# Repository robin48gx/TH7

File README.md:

# TH7
Code to read up to seven thermocouple inputs  from the raspberry pi using the SDS TH7 PCB

Enable spi in raspi-config.

Also, if you are running the pi as a user other than 'pi' add yourself to the spi group 
in /etc/group.

Clone the git hub repo here,

    $ git clone https://github.com/robin48gx/TH7.git 

change directory to TH7 and then run

    $ python ssh_terminal_TH7.py

The python file ssh_terminal_TH7.py is a simple terminal program
that displays the microvolts received from
the thermocouples and displays them in centigrade (for `k` type).
It also displays the PCB temperature and  the Vcc (voltage from USB to the pi;
the value is necessary for accurate calculation of microvolts).
It also creates a logging file (called 'TH7.log') showing the voltage supplied to the pi, the 
PCB temperature and the temperature of each connected thermocouple. This logs once per minute.
If logging is required run with nohup, i.e.

    $ nohup python TH7_logger.py > /dev/null & 
    
The logging will then continue on the pi even if the terminal running it is closed.
The LEDs are controlled by the ssh_terminal_TH7.py and by the TH7_logger.py programs, so if they are alternately blinking
this means the logging is continuing.
A script called 'plot_it.sh' will (using gnuplot) take data from the TH7.log file
and present it as a graph.

The python file thermometers_TH7.py adds to this with 
tkinter drawn thermometers. You may need the tkinter python 
modules for this : i.e. apt-get install python-tk.

Feel free to branch off this to make a temperature logger or a web interface.

For h/w 0.4 and above, an open thermocouple connection will display a very low 
micro-volts figure (typically < -7000) which is out of range for most thermocouples
and out of the range that most temperature readings would ever require (its below
abs zero for a k type for instance).
This means open thermocouples can be error flagged (as has been implemented for the
python `k` type thermocouple in this repo).

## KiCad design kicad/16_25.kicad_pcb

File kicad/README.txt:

The TH7 project in these files is named test.
It is at hardware revision 0.3

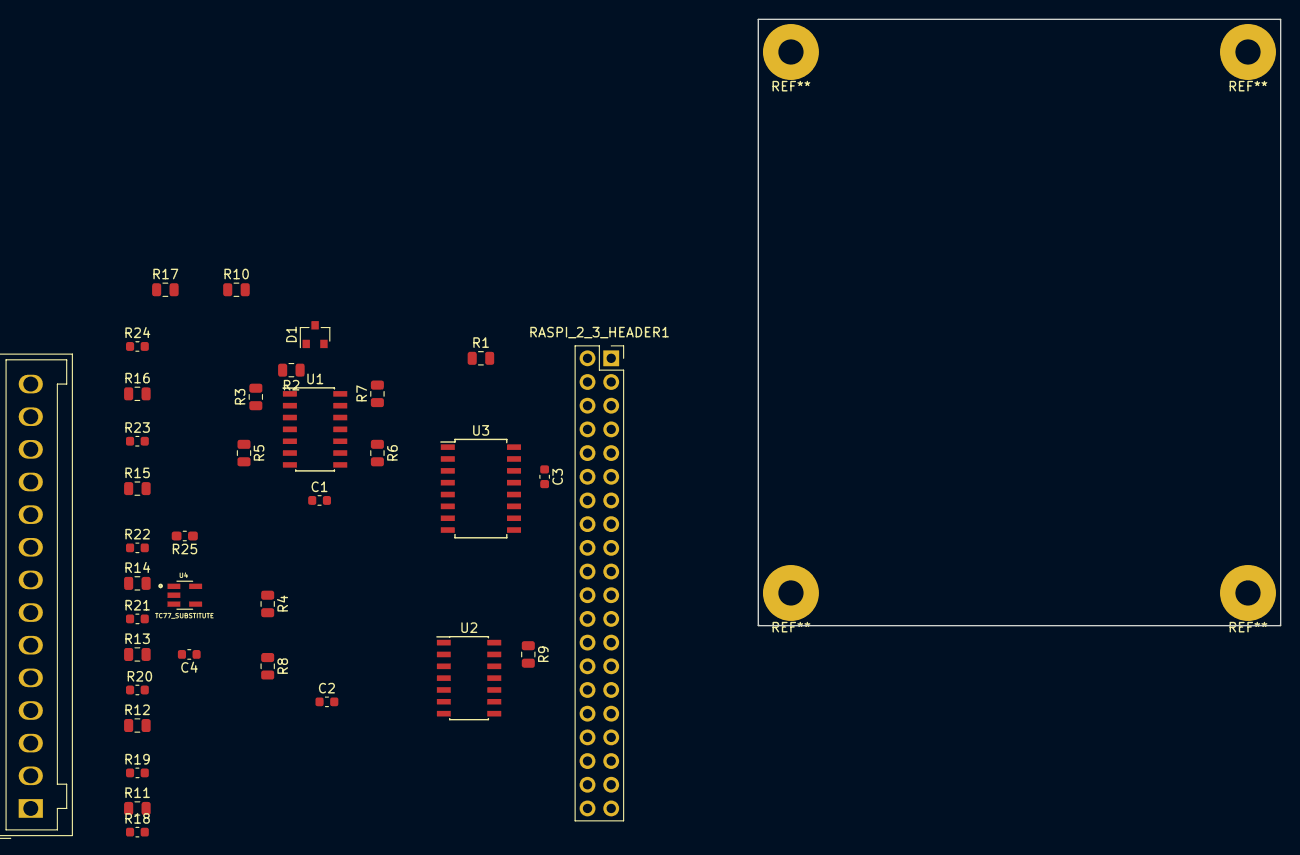
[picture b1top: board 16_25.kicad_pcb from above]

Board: 2 copper layers, 56.0 x 65.0 mm, 36 parts (0 on the bottom side), 44 nets, no tracks yet.

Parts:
C1, C2, C3, C4: 100nF; C_0603_1608Metric
D1: LM4040DBZ-4.1; SOT-23
J1: Screw_Terminal_01x14; Wago_734-144_1x14_P3.50mm_Vertical
R1: 470; R_0805_2012Metric
R2, R3: 10k; R_0805_2012Metric
R4: 200K; R_0805_2012Metric
R5, R6, R7: 100K; R_0805_2012Metric
R8, R10: 200k; R_0805_2012Metric
R9: 500k; R_0805_2012Metric
R11: 1K; R_0805_2012Metric
R12, R13, R14, R15, R16, R17: 1k; R_0805_2012Metric
R18, R19, R20, R21, R22, R23, R24: 500K; R_0603_1608Metric
R25: 10K; R_0603_1608Metric_Pad1.05x0.95mm_HandSolder
RASPI_2_3_HEADER1: Raspberry_Pi_2_3; PinSocket_2x20_P2.54mm_Vertical
U1, U2: MCP6074-E_SL; SOIC-14_3.9x8.7mm_P1.27mm
U3: MCP3208; SOIC-16W_5.3x10.2mm_P1.27mm
U4: TC77_SUBSTITUTE; SOT95P280X145-5N

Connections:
4V096: R3.2, R18.2, R19.2, R20.2, R21.2, R22.2, R23.2, R24.2, U1.1, U1.5, U1.10, U1.12, U2.3, U2.5, U2.10, U2.12, U3.1
unnamed: C1.1, C2.1, RASPI_2_3_HEADER1.4, RASPI_2_3_HEADER1.39, U1.4, U2.4
unnamed: C1.2, C2.2, RASPI_2_3_HEADER1.25, U1.11, U2.11
unnamed: C3.1, C4.1, R1.2, RASPI_2_3_HEADER1.2, U3.15, U3.16, U4.5
unnamed: C3.2, RASPI_2_3_HEADER1.30, U3.9
unnamed: C4.2, R25.2, RASPI_2_3_HEADER1.20, U4.2
unnamed: D1.1, R1.1, R2.2
unnamed: D1.2, RASPI_2_3_HEADER1.6
unnamed: J1.1, R18.1
unnamed: J1.2, R11.1
unnamed: J1.3, R19.1
unnamed: J1.4, R12.1
unnamed: J1.5, R20.1
unnamed: J1.6, R13.1
unnamed: J1.7, R21.1
unnamed: J1.8, R14.1
unnamed: J1.9, R22.1
unnamed: J1.10, R15.1
unnamed: J1.11, R23.1
unnamed: J1.12, R16.1
unnamed: J1.13, R24.1
unnamed: J1.14, R17.1
unnamed: R2.1, U1.3
unnamed: R3.1, U1.2
unnamed: R4.1, U2.1, U3.5
unnamed: R5.2, U1.7, U3.2
unnamed: R6.2, U1.8, U3.3
unnamed: R7.2, U1.14, U3.4
unnamed: R8.2, U2.7
unnamed: R9.1, U2.14
unnamed: R10.1, R17.2, U2.9, U3.7
unnamed: R10.2, U2.8
unnamed: R9.2, R11.2, U2.13, U3.8
unnamed: R5.1, R12.2, U1.6
unnamed: R6.1, R13.2, U1.9
unnamed: R7.1, R14.2, U1.13
unnamed: R4.2, R15.2, U2.2
unnamed: R8.1, R16.2, U2.6, U3.6
unnamed: R25.1, RASPI_2_3_HEADER1.21, U3.12, U4.4
unnamed: RASPI_2_3_HEADER1.19, U3.11
unnamed: RASPI_2_3_HEADER1.23, U3.13, U4.3
unnamed: RASPI_2_3_HEADER1.24, U3.10
unnamed: RASPI_2_3_HEADER1.26, U4.1
unnamed: RASPI_2_3_HEADER1.34, U3.14

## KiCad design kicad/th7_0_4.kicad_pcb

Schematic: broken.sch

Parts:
C1, C2, C3, C4: 100nF; C_0603_1608Metric
D1: LM4040DBZ-4.1; SOT-23
D2, D3: LED_ALT; LED_0805_2012Metric_Pad1.15x1.40mm_HandSolder
J1: Screw_Terminal_01x14; Wago_734-144_1x14_P3.50mm_Vertical
R1: 470; R_0805_2012Metric
R2, R3: 10k; R_0805_2012Metric
R4, R5, R6, R7, R8, R9, R10: 100K; R_0805_2012Metric
R11: 1K; R_0805_2012Metric
R12, R13, R14, R15, R16, R17: 1k; R_0805_2012Metric
R18, R19: 330; R_0805_2012Metric
R25: 10K; R_0603_1608Metric_Pad1.05x0.95mm_HandSolder
R31, R32, R33, R34, R35, R36, R37: 330k; R_0805_2012Metric
RASPI_2_3_HEADER1: Raspberry_Pi_2_3; PinSocket_2x20_P2.54mm_Vertical
U1, U2: MCP6074-E_SL; SOIC-14_3.9x8.7mm_P1.27mm
U3: MCP3208; SOIC-16W_5.3x10.2mm_P1.27mm
U4: TC77_SUBSTITUTE; SOT95P280X145-5N

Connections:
4V096: U1.1 (VOUTA), U1.5 (VINB+), U1.10 (VINC+), U1.12 (VIND+), U2.3 (VINA+), U2.5 (VINB+), U2.10 (VINC+), U2.12 (VIND+); also elsewhere on the board
5V: U1.4 (VDD), U2.4 (VDD), U4.5 (Vdd); also elsewhere on the board
CE1: U4.1 (CS); also elsewhere on the board
MISO_0: U4.4 (SIO); also elsewhere on the board
unnamed 18: U1.3 (VINA+); also elsewhere on the board
unnamed 19: U1.2 (VINA); also elsewhere on the board
unnamed 20: U2.1 (VOUTA); also elsewhere on the board
unnamed 21: U1.7 (VOUTB); also elsewhere on the board
unnamed 22: U1.8 (VOUTC); also elsewhere on the board
unnamed 23: U1.14 (VOUTD); also elsewhere on the board
unnamed 24: U2.7 (VOUTB); also elsewhere on the board
unnamed 25: U2.14 (VOUTD); also elsewhere on the board
unnamed 26: U2.9 (VINC); also elsewhere on the board
unnamed 27: U2.8 (VOUTC); also elsewhere on the board
unnamed 28: U2.13 (VIND); also elsewhere on the board
unnamed 29: U1.6 (VINB); also elsewhere on the board
unnamed 30: U1.9 (VINC); also elsewhere on the board
unnamed 31: U1.13 (VIND); also elsewhere on the board
unnamed 32: U2.2 (VINA); also elsewhere on the board
unnamed 33: U2.6 (VINB); also elsewhere on the board
SCLK0: U4.3 (SCK); also elsewhere on the board

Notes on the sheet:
Revision 0.4 330k disconnection resistors

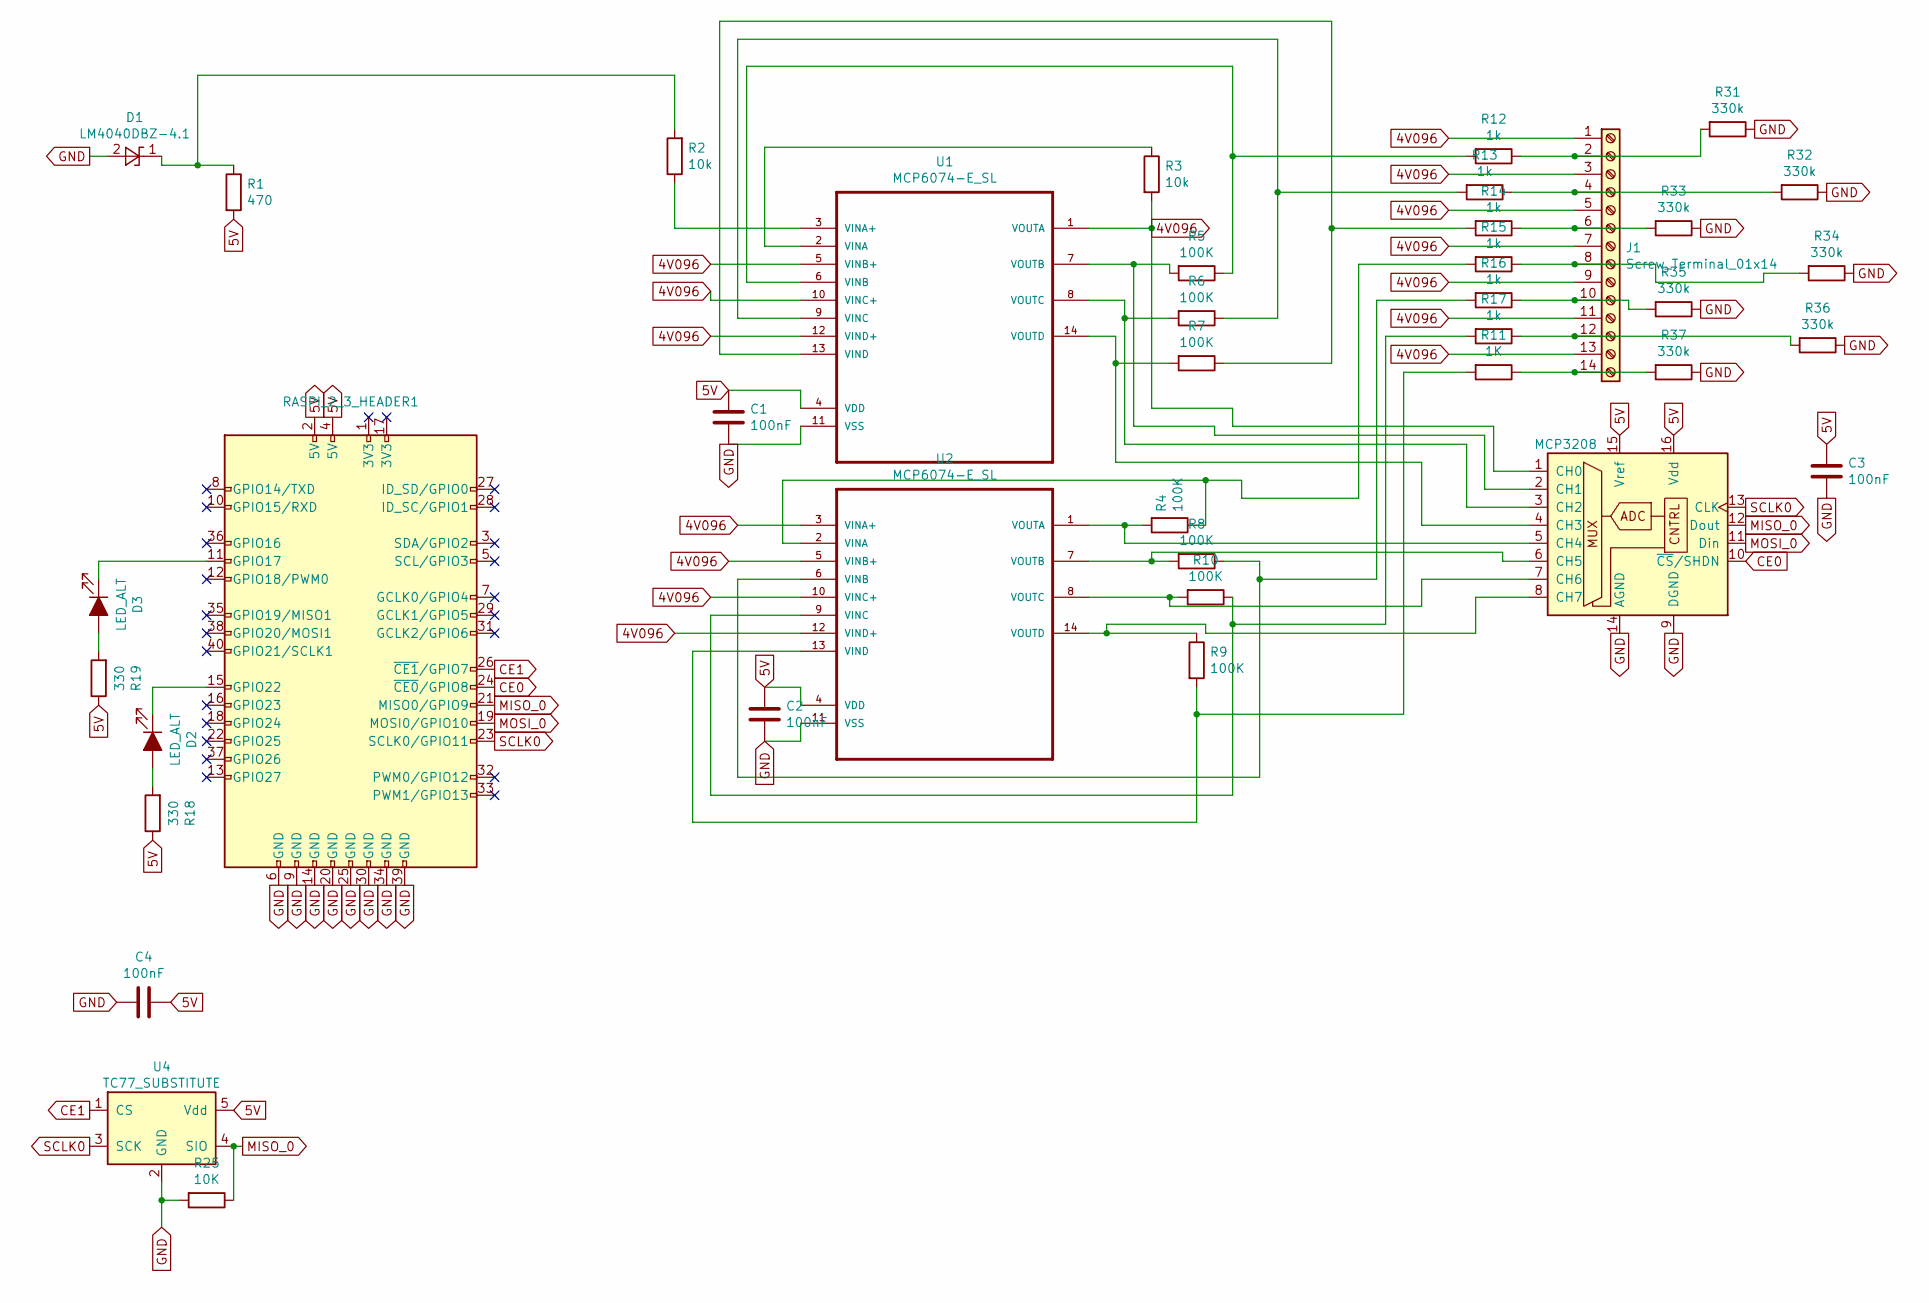
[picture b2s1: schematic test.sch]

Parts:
C1, C2, C3, C4: 100nF; C_0603_1608Metric
D1: LM4040DBZ-4.1; SOT-23
D2, D3: LED_ALT; LED_0805_2012Metric_Pad1.15x1.40mm_HandSolder
J1: Screw_Terminal_01x14; Wago_734-144_1x14_P3.50mm_Vertical
R1: 470; R_0805_2012Metric
R2, R3: 10k; R_0805_2012Metric
R4, R5, R6, R7, R8, R9, R10: 100K; R_0805_2012Metric
R11: 1K; R_0805_2012Metric
R12, R13, R14, R15, R16, R17: 1k; R_0805_2012Metric
R18, R19: 330; R_0805_2012Metric
R25: 10K; R_0603_1608Metric_Pad1.05x0.95mm_HandSolder
R31, R32, R33, R34, R35, R36, R37: 330k; R_0805_2012Metric
RASPI_2_3_HEADER1: Raspberry_Pi_2_3; PinSocket_2x20_P2.54mm_Vertical
U1, U2: MCP6074-E_SL; SOIC-14_3.9x8.7mm_P1.27mm
U3: MCP3208; SOIC-16W_5.3x10.2mm_P1.27mm
U4: TC77_SUBSTITUTE; SOT95P280X145-5N

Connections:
4V096: J1.1, J1.3, J1.5, J1.7, J1.9, J1.11, J1.13, R3.2, U1.1 (VOUTA), U1.5 (VINB+), U1.10 (VINC+), U1.12 (VIND+), U2.3 (VINA+), U2.5 (VINB+), U2.10 (VINC+), U2.12 (VIND+), U3.1 (CH0); also elsewhere on the board
5V: C1.1, C2.1, C3.1, C4.1, R1.2, R18.1, R19.1, RASPI_2_3_HEADER1.2 (5V), RASPI_2_3_HEADER1.4 (5V), U1.4 (VDD), U2.4 (VDD), U3.15 (Vref), U3.16 (Vdd), U4.5 (Vdd); also elsewhere on the board
CE0: RASPI_2_3_HEADER1.24 (~CE0~/GPIO8), U3.10 (~CS~/SHDN)
CE1: RASPI_2_3_HEADER1.26 (~CE1~/GPIO7), U4.1 (CS)
MISO_0: R25.1, RASPI_2_3_HEADER1.21 (MISO0/GPIO9), U3.12 (Dout), U4.4 (SIO)
MOSI_0: RASPI_2_3_HEADER1.19 (MOSI0/GPIO10), U3.11 (Din)
unnamed: D1.1 (K), R1.1, R2.2
unnamed: D2.1 (K), RASPI_2_3_HEADER1.15 (GPIO22)
unnamed: D2.2 (A), R18.2
unnamed: D3.1 (K), RASPI_2_3_HEADER1.11 (GPIO17)
unnamed: D3.2 (A), R19.2
unnamed: J1.2, R12.1, R31.2
unnamed: J1.4, R13.1, R32.2
unnamed: J1.6, R14.1, R33.2
unnamed: J1.8, R15.1, R34.2
unnamed: J1.10, R16.1, R35.2
unnamed: J1.12, R17.1, R36.2
unnamed: J1.14, R11.1, R37.2
unnamed: R2.1, U1.3 (VINA+)
unnamed: R3.1, U1.2 (VINA)
unnamed: R4.2, U2.1 (VOUTA), U3.5 (CH4)
unnamed: R5.2, U1.7 (VOUTB), U3.2 (CH1)
unnamed: R6.2, U1.8 (VOUTC), U3.3 (CH2)
unnamed: R7.2, U1.14 (VOUTD), U3.4 (CH3)
unnamed: R8.2, U2.7 (VOUTB), U3.6 (CH5)
unnamed: R9.1, U2.14 (VOUTD), U3.8 (CH7)
unnamed: R10.1, R17.2, U2.9 (VINC)
unnamed: R10.2, U2.8 (VOUTC), U3.7 (CH6)
unnamed: R9.2, R11.2, U2.13 (VIND)
unnamed: R5.1, R12.2, U1.6 (VINB)
unnamed: R6.1, R13.2, U1.9 (VINC)
unnamed: R7.1, R14.2, U1.13 (VIND)
unnamed: R4.1, R15.2, U2.2 (VINA)
unnamed: R8.1, R16.2, U2.6 (VINB)
SCLK0: RASPI_2_3_HEADER1.23 (SCLK0/GPIO11), U3.13 (CLK), U4.3 (SCK)

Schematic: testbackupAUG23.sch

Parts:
C1, C2, C3, C4: 100nF; C_0603_1608Metric
D1: LM4040DBZ-4.1; SOT-23
J1: Screw_Terminal_01x14; Wago_734-144_1x14_P3.50mm_Vertical
R1: 470; R_0805_2012Metric
R2, R3: 10k; R_0805_2012Metric
R4, R5, R6, R7, R8, R9, R10: 100K; R_0805_2012Metric
R11: 1K; R_0805_2012Metric
R12, R13, R14, R15, R16, R17: 1k; R_0805_2012Metric
R25: 10K; R_0603_1608Metric_Pad1.05x0.95mm_HandSolder
RASPI_2_3_HEADER1: Raspberry_Pi_2_3; PinSocket_2x20_P2.54mm_Vertical
U1, U2: MCP6074-E_SL; SOIC-14_3.9x8.7mm_P1.27mm
U3: MCP3208; SOIC-16W_5.3x10.2mm_P1.27mm
U4: TC77_SUBSTITUTE; SOT95P280X145-5N

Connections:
4V096: U1.1 (VOUTA), U1.5 (VINB+), U1.10 (VINC+), U1.12 (VIND+), U2.3 (VINA+), U2.5 (VINB+), U2.10 (VINC+), U2.12 (VIND+); also elsewhere on the board
5V: U1.4 (VDD), U2.4 (VDD); also elsewhere on the board
unnamed 18: U1.3 (VINA+); also elsewhere on the board
unnamed 19: U1.2 (VINA); also elsewhere on the board
unnamed 20: U2.1 (VOUTA); also elsewhere on the board
unnamed 21: U1.7 (VOUTB); also elsewhere on the board
unnamed 22: U1.8 (VOUTC); also elsewhere on the board
unnamed 23: U1.14 (VOUTD); also elsewhere on the board
unnamed 24: U2.7 (VOUTB); also elsewhere on the board
unnamed 25: U2.14 (VOUTD); also elsewhere on the board
unnamed 26: U2.9 (VINC); also elsewhere on the board
unnamed 27: U2.8 (VOUTC); also elsewhere on the board
unnamed 28: U2.13 (VIND); also elsewhere on the board
unnamed 29: U1.6 (VINB); also elsewhere on the board
unnamed 30: U1.9 (VINC); also elsewhere on the board
unnamed 31: U1.13 (VIND); also elsewhere on the board
unnamed 32: U2.2 (VINA); also elsewhere on the board
unnamed 33: U2.6 (VINB); also elsewhere on the board

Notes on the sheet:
T/C 1 +ve
T/C 1 -ve

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
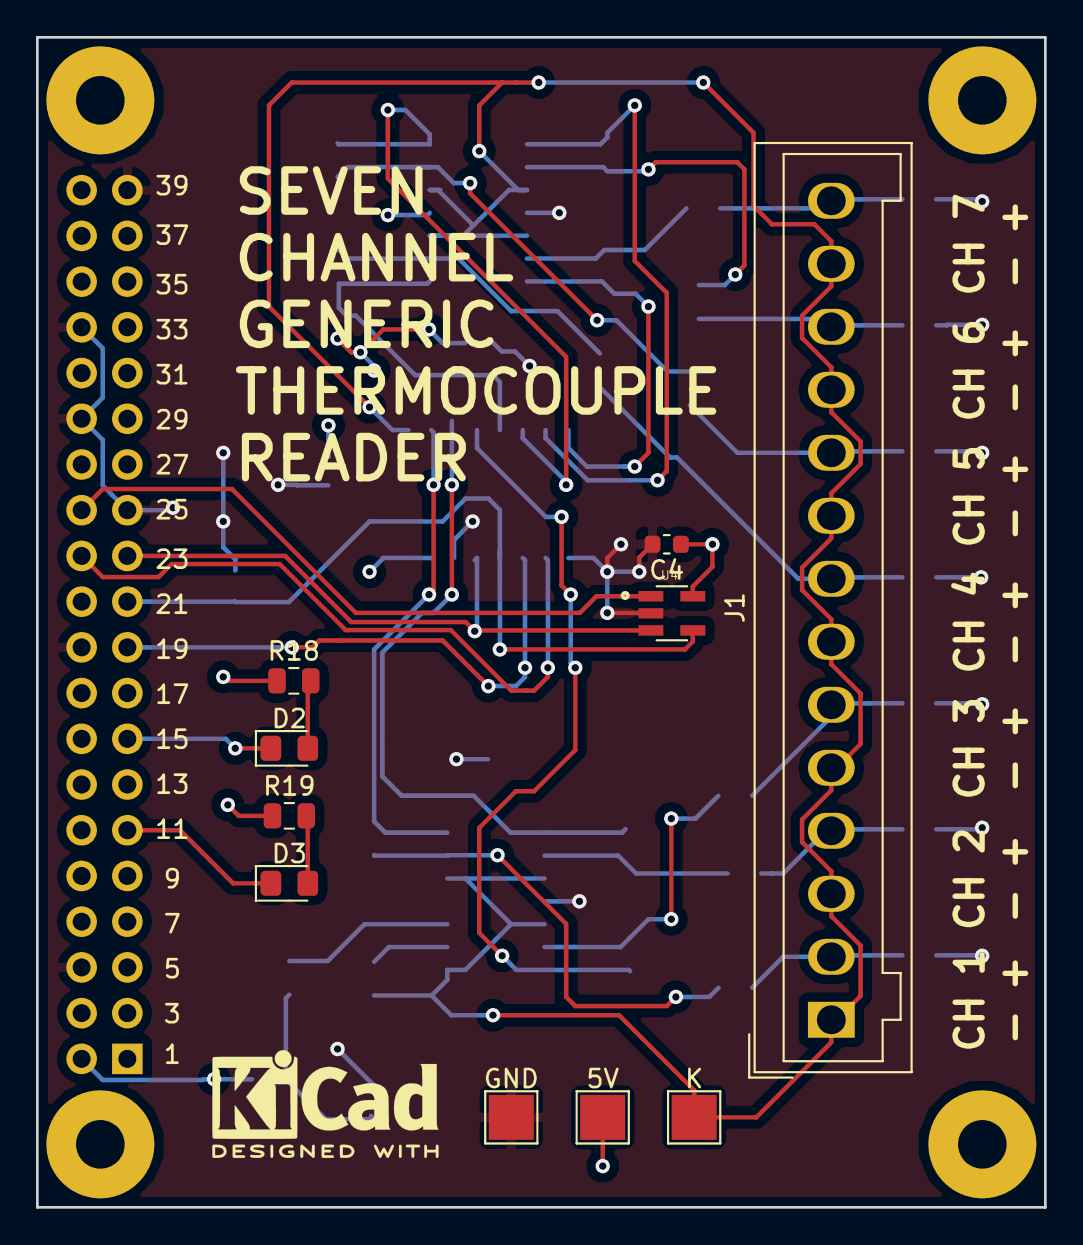
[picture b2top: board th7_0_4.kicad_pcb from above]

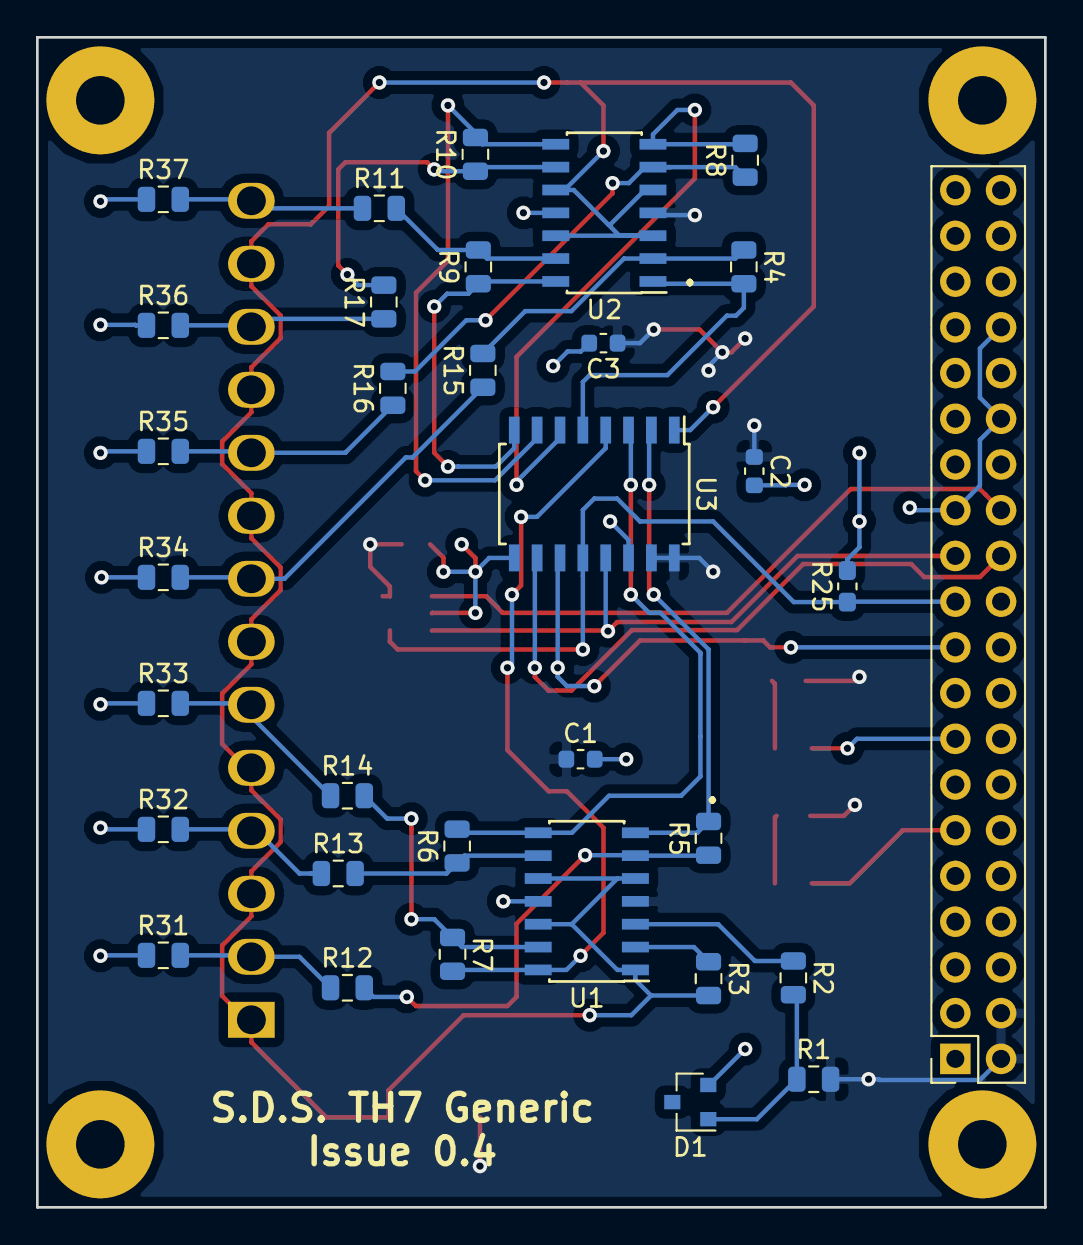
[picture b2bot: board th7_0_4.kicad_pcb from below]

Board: 2 copper layers, 56.0 x 65.0 mm, 43 parts (33 on the bottom side), 36 nets.

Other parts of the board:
5V: TestPoint_Pad_2.5x2.5mm
GND: TestPoint_Pad_2.5x2.5mm
K: TestPoint_Pad_2.5x2.5mm

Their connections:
4V096: K.1; also elsewhere on the board
5V: 5V.1; also elsewhere on the board

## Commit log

2018-09-10 Python program to read seven `k' type thermocouples using the SDS TH7 PCB that fits onto the raspberry pi
2018-09-11 image of unpopulated 0.3 PCB seven channel thermocouple reader for raspberry pi
2018-09-12 User LEDS alternately turned on and off slowly
2018-09-14 Using micro volts adds instead of simpler pcb_temp add for increased accuracY
2018-09-14 display micro-volts as corrected for from zero centigrade
2018-09-14 fixed polynomial for > 20.X mV
2018-09-28 Update README.md
    Added getting started instructions.
2018-09-28 Mark < 6.5mV as error (this is below abs zero and is picked up by the disconnect protection resistor (if fitted)
2018-10-08 OPEN thermo-couple detection description
    OPEN thermo-couple detection description
2018-10-08 spelling/typo
2018-10-16 TH7 0.4 reading from a K type probe
2018-10-23 Thermocouple tkinter demo using random numbers
2018-10-23 renamed the original terminal temp display python program
2018-10-23 Linked spi voltage /tc77 reading code with the thermometer gui
2018-10-23 commented the code a little
2018-10-23 comments
2018-10-23 faster updates, INTERVAL now 1mS
2018-10-25 python global pcb_temp
2018-10-27 doicumentation:
2018-10-27 documentation:
2018-10-27 Typos
2018-10-27 documentation: Made into a fold up leaflet
2018-10-28 black and white leaflet
2018-10-28 documentation: colour leaflet
2018-10-28 colour photos back
2018-10-28 documentation: colour photos included in git now
2018-10-28 documentation: colour leaflet in pdf
2018-11-10 Added logging to the ssh script
2018-11-18 compressed the thermometer scaling
2018-11-18 colour change on 100oC
2018-11-19 Leaflet and customisation
2018-11-19 added pdf to repo
2019-01-03 ploting script to call gnuplot for channel 1 long term graphing
2019-01-04 more meaningful graph name
2019-01-21 Compression more accurate
2019-01-29 pdf of fold up leaflet added
2019-04-24 added voltage error warning
2019-06-16 TH7_logger created so that the TH7_alive script can restart it. TH7_alive.sh should be used with crontab to ensure the TH7 process is running.
2019-06-16 Crontab verified restarting TH7_logger with the TH7_alive.sh script.
2019-06-16 Now logging to TH7.db
2019-06-16 Fixed timed data logging.
2019-06-16 Update README.md
    TH7_logger.py now added. This updates an sqlite3 database as well as producing a text log file.
2019-10-10 TH7_alive.sh script used by crontab to restart the TH7_logger.py script which writes temerature data to an SQlite Database.
2020-05-10 typos in leaflet
2020-05-10 typos leaflet
2020-05-10 leaflet typos
2020-05-12 test code for new thermocouple types, J and N.
2020-05-12 Test to see if this works
2020-05-12 fixed?
2020-05-12 might have fixed it
2020-05-12 using numpy because for some reason python doesnt have arrays
2020-05-12 forgot to remove parenthesises
2020-05-12 testing
2020-05-12 fixed imports
2020-05-12 fixed imports again
2020-05-12 suitable replacement soon
2020-05-12 done graphs
2020-05-12 forgot this file
2020-05-12 adding a configurable python declaration so that mixed T/Cs can be used easily on one TH7.
2020-05-12 Added a description of channel configuration.
2020-05-12 added support for E -type thermocouples
2020-05-12 fixed a few bugs relating to printing microvolt and a few typos in the thermocouples file.
2020-05-12 added a starter value at a few oC to reduce F=3 wait but not affecting its "ability."
2020-05-13 Added polynomials and software support for B-type thermocouples.
2020-05-13 fixed a typo
2020-05-13 Added polynomials and software support for R-type thermocouples.
2020-05-13 added polynomials and software support for the S-type thermocouples.
2020-05-13 fixed a typo and missing paren
2020-05-13 missing paren
2020-05-16 first attempt at introducing sqlite3 datalogging
2020-05-16 nothing is really working atm will fix tomorrow
2020-05-19 first attempt at offset
2020-05-19 fixed offsets
2020-05-25 altered filtering startup
2020-05-27 early development for graphing of Th7 standard logging utility's log files
2020-06-18 preparing for merge with master
2020-06-18 Update ssh_terminal_TH7.py
    display as ip only
2020-06-18 Enabled all channels by default
2020-06-20 Added configurable gain calibration per channel basis, so that thermocouple channels (independent of type) can be calibrated to within 0.1 degrees celsius.
2020-07-25 Added LED blinking
2020-12-31 Compatability with JSON web diplay project, using built in python3 `http.server' module.
2021-01-01 fixed json and added error detection -300 oC if uV is too small
2021-01-25 Update ssh_terminal_TH7.py
    All channels now start with/use default offset and gain values
2021-10-22 kicad files
2022-10-15 th7 gui first draft
2022-10-15 gui experi,emts
2022-10-15 why does the PushButton call the call back on init? This seems utterly stupid
2022-10-15 OK first page of the GUI done. Need to learn how to make the configure window come up now
2022-10-15 OK looks neat now. Lambda function still puzzling as to why exactly required.
2022-10-15 OK got a window with calibration factors working
2022-10-15 actually works now after passing the actual TextBox objects. Lambda! Lambda! Lammbda!
2022-10-15 bit of syntax checking and confirmation of set calibration
2022-11-05 reindented. also if the micro-volts are out by 1000 reset the filter for the microvolts (uv) rather than on startup
2022-11-05 Update ssh_terminal_TH7.py
    Faster reset of micro-volts (i.e. if >= 1000uV different resets micro-volt filter)
2022-11-26 Got the gui up and calling the caode to calculate the thermocouples. need to connect the GUI up now to other parts
2022-11-26 GUI version in separate branch
2024-11-09 Skeleton GUI using TKINTER, includes idle call back which can be connected to the existing TH7 python code.
2024-11-09 widgets indexed by strings
2024-11-09 GUI displaying actual TH7 live data
2024-11-09 more GUI work can pick settings for each channel etc, needs LOAD/SAVE buttons
2024-11-10 added vref,pcbtemp fields, load and save buttons, submit became reply. Removed pull down on Ch 7 for test, does not appear to alter measurement ie not loaded too harshly (t/c). Note 4.1V is at the OP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
2024-12-07 gui now saves/loads/applies config
2024-12-07 forgot a minus
2024-12-07 startup code fix and python3 shebang
2025-02-22 kalman filter added as filter 5 now by default
2025-02-23 2D Kalman added to speed up small changes in temp.
2025-04-11 Logs JSON when enable logging check box ticked to TH7.log
